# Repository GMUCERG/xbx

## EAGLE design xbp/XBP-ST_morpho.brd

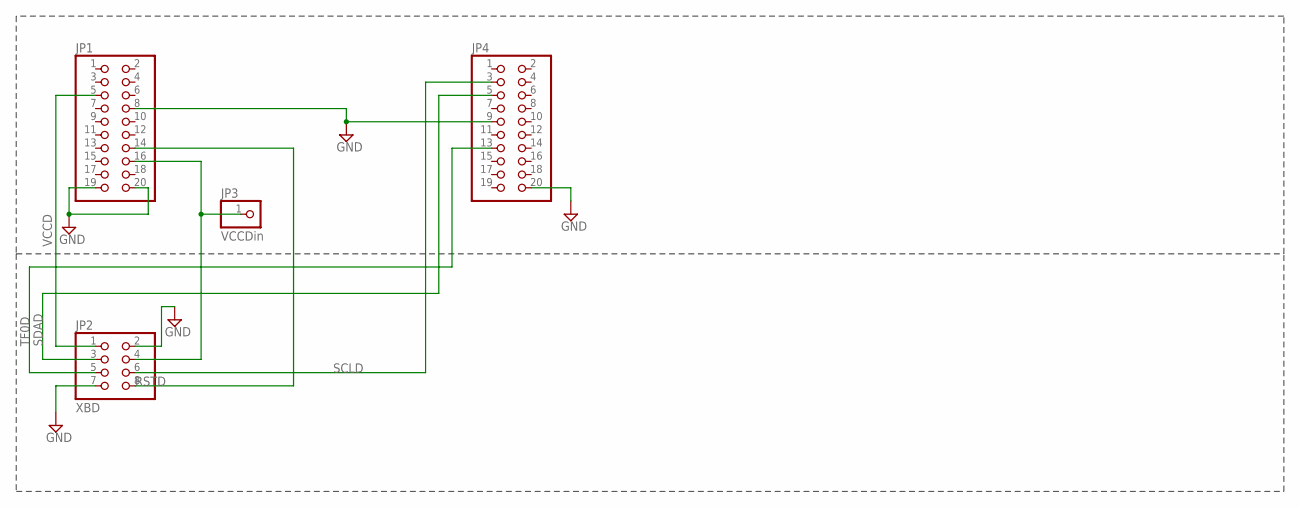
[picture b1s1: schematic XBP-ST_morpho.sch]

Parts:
JP1, JP4: PINHD-2X10; 2X10
JP2: XBD; 2X04/90
JP3: VCCDin; 1X01

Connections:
GND: JP1.8, JP1.19, JP1.20, JP2.2, JP2.7, JP4.9, JP4.20
unnamed: JP1.16, JP2.4, JP3.1
RSTD: JP1.14, JP2.8
SCLD: JP2.6, JP4.3
SDAD: JP2.3, JP4.5
TF0D: JP2.5, JP4.13
VCCD: JP1.5, JP2.1

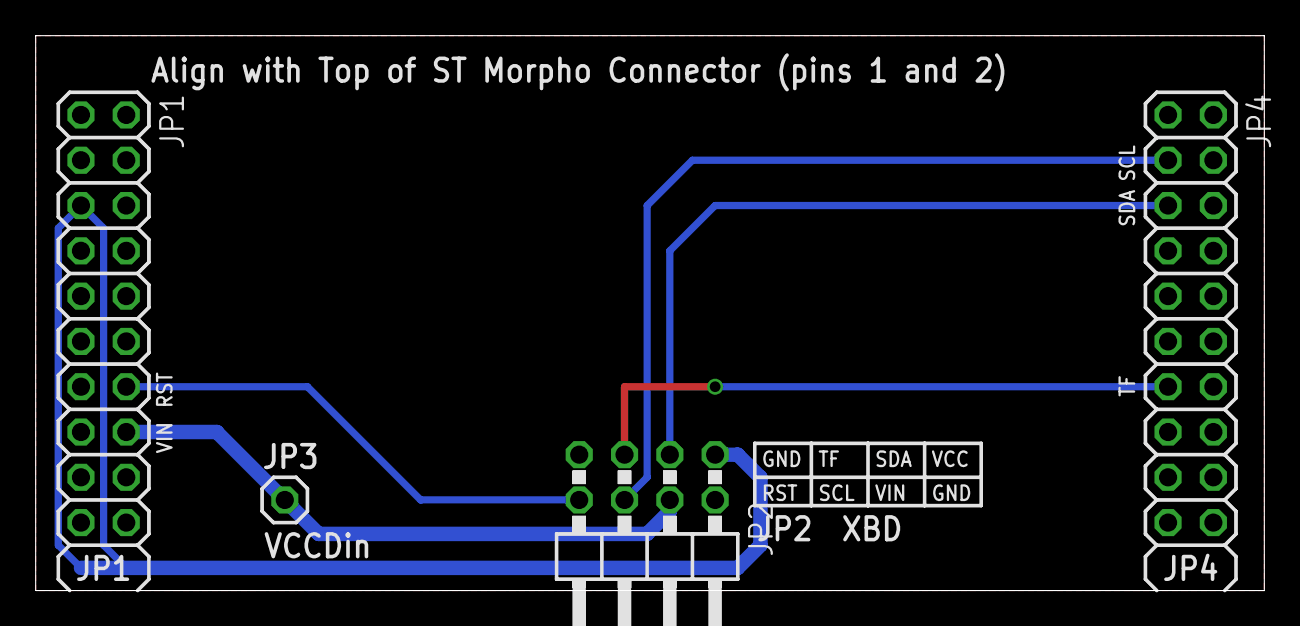
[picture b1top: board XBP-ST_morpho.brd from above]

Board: 2 copper layers, 68.9 x 31.1 mm, 4 parts (0 on the bottom side), 7 nets.

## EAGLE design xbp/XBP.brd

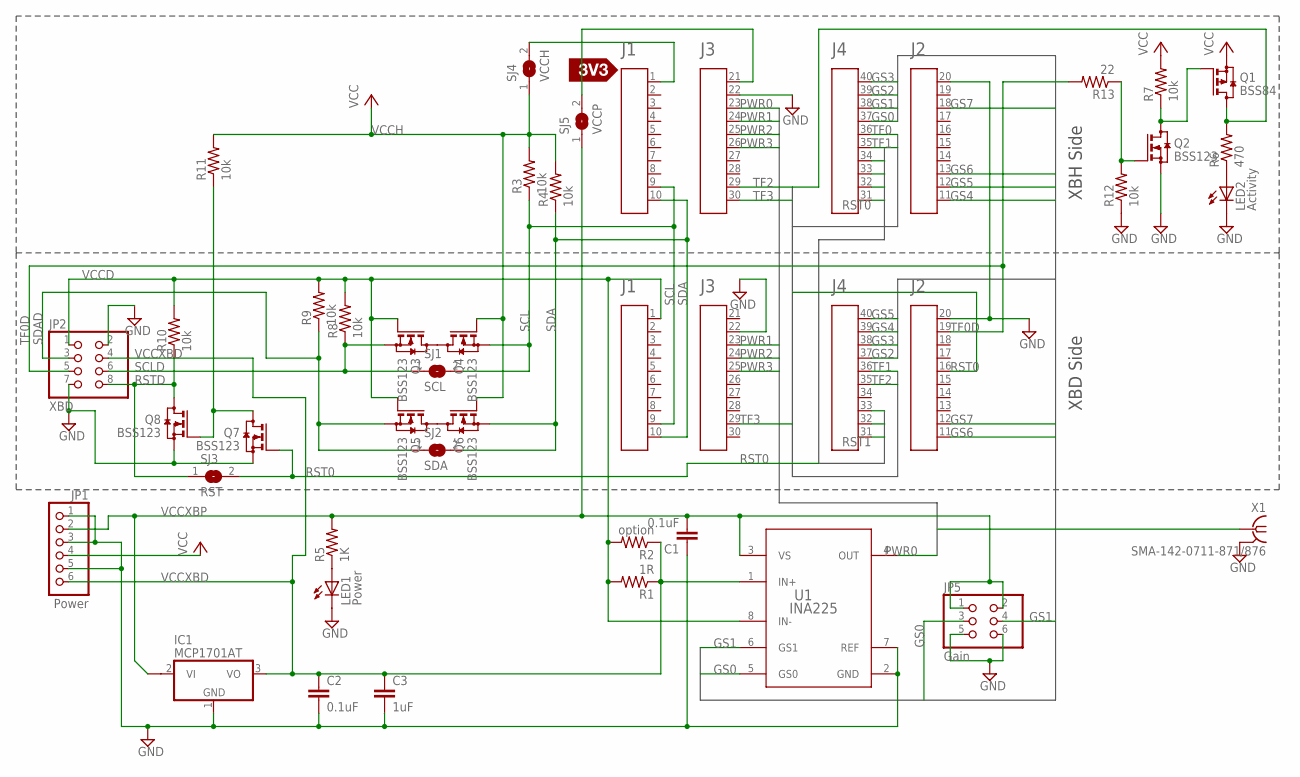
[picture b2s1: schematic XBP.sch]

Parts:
A1: XBHCon; 4X10-BOOSTERPACK
A2: XBDCon; 4X10-BOOSTERPACK
C1, C2: 0.1uF; C0603
C3: 1uF; C0603
IC1: MCP1701AT; SOT89
JP1: Power; 1X06/90
JP2: XBD; 2X04/90
JP5: Gain; 2X03
LED1: Power; CHIPLED_0603
LED2: Activity; CHIPLED_0603
Q1: BSS84; SOT23
Q2, Q3, Q4, Q5, Q6, Q7, Q8: BSS123; SOT23
R1: 1R; R1210
R2: option; R0805
R3, R4, R7, R8, R9, R10, R11, R12: 10k; R0603
R5: 1K; R0603
R6: 470; R0603
R13: 22; R0603
SJ1: SCL; SJ
SJ2: SDA; SJ
SJ3: RST; SJ
SJ4: VCCH; SJ
SJ5: VCCP; SJ
U1: INA225; DGK0008A_N
U3: SILK_3V3_TAG
X1: SMA-142-0711-871/876; J502-ND-142-0711-871/876

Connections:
GND: A1.20, A1.22, A2.20, A2.22, C1.1, C2.2, C3.2, IC1.1 (GND), JP1.1, JP1.3, JP1.5, JP2.2, JP2.7, JP5.5, JP5.6, LED1.C, LED2.C, Q2.2 (S), Q7.2 (S), Q8.2 (S), R12.1, U1.2 (GND), U1.7 (REF), X1.G@1 (2), X1.G@2 (2), X1.G@3 (2), X1.G@4 (2)
GS0: A1.37, JP5.3, U1.5 (GS0)
GS1: A1.38, JP5.4, U1.6 (GS1)
GS2: A1.39, A2.37
GS3: A1.40, A2.38
GS4: A1.11, A2.39
GS5: A1.12, A2.40
GS6: A1.13, A2.11
GS7: A1.18, A2.12
unnamed: A1.1, SJ4.2
unnamed: A1.21, SJ5.2
unnamed: LED1.A, R5.1
unnamed: Q2.1 (G), R12.2, R13.1
unnamed: LED2.A, R6.1
unnamed: Q3.3 (D), Q4.3 (D)
unnamed: Q5.3 (D), Q6.3 (D)
unnamed: Q1.1 (G), Q2.3 (D), R7.1
unnamed: Q7.3 (D), Q8.1 (G), R11.1
PWR0: A1.23, U1.4 (OUT), X1.1
PWR1: A1.24, A2.23
PWR2: A1.25, A2.24
PWR3: A1.26, A2.25
RST0: A1.31, A2.16, Q7.1 (G), SJ3.2
RST1: A1.32, A2.31
RST2: A1.33, A2.32
RST3: A1.34, A2.33
RSTD: JP2.8, Q8.3 (D), R10.1, SJ3.1
SCL: A1.9, A2.9, Q4.2 (S), R3.1, SJ1.2
SCLD: JP2.6, Q3.2 (S), R8.1, SJ1.1
SDA: A1.10, A2.10, Q6.2 (S), R4.1, SJ2.2
SDAD: JP2.3, Q5.2 (S), R9.1, SJ2.1
TF0: A1.36, Q1.3 (D), R6.2
TF0D: A2.19, JP2.5, R13.2
TF1: A1.35, A2.36
TF2: A1.29, A2.35
TF3: A1.30, A2.29
VCCD: A2.1, JP2.1, Q3.1 (G), Q5.1 (G), R1.2, R2.2, R8.2, R9.2, R10.2, U1.8 (IN-)
VCCH: JP1.4, Q1.2 (S), Q4.1 (G), Q6.1 (G), R3.2, R4.2, R7.2, R11.2, SJ4.1
VCCXBD: C2.1, C3.1, IC1.3 (VO), JP1.6, JP2.4, R1.1, R2.1, U1.1 (IN+)
VCCXBP: C1.2, IC1.2@1 (VI1), JP1.2, JP5.1, JP5.2, R5.2, SJ5.1, U1.3 (VS)

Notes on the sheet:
XBH Side
XBD Side

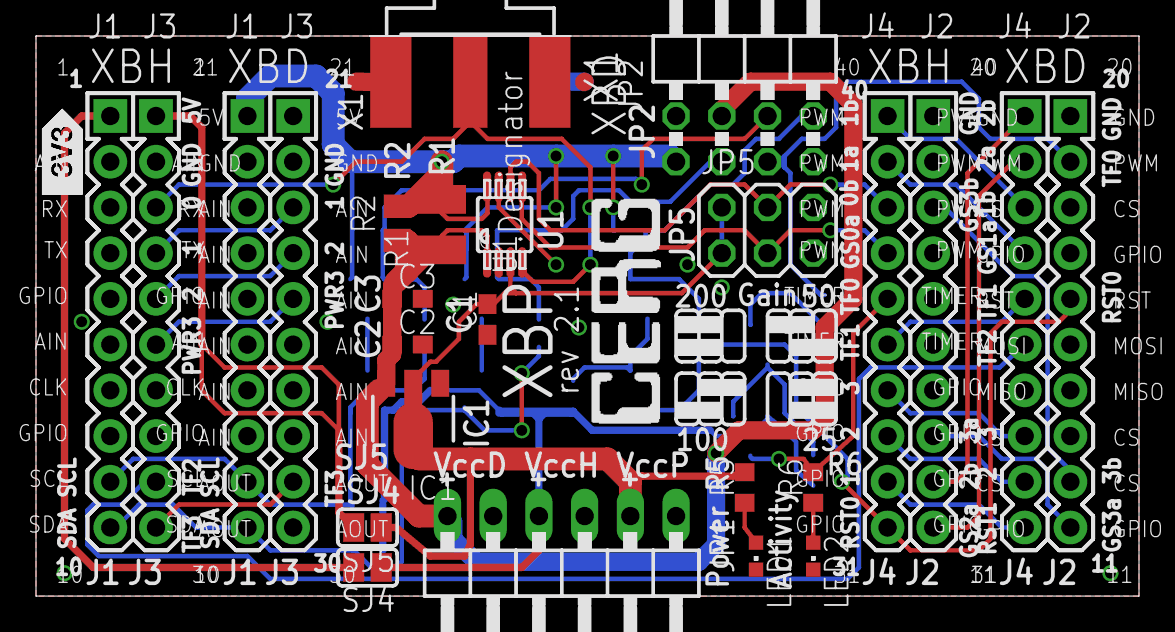
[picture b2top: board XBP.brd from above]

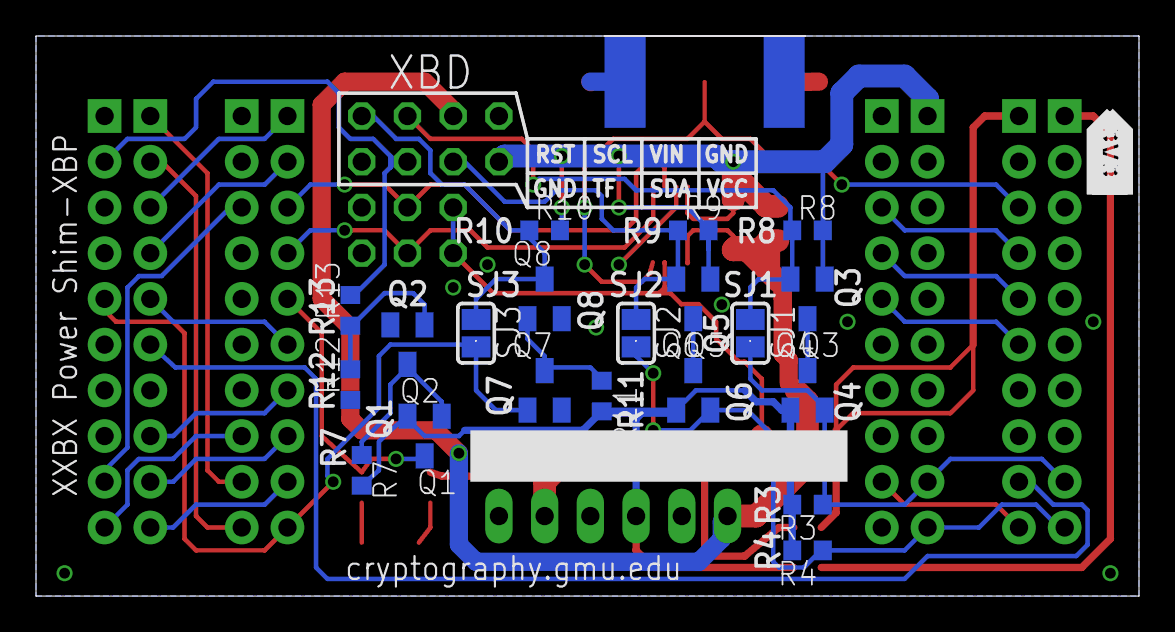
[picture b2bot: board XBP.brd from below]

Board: 2 copper layers, 61.3 x 31.1 mm, 40 parts (20 on the bottom side), 40 nets.

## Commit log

2015-09-01 Make submodules track master
2015-09-01 Update instructions, install script
2015-09-07 Fix instructions
    add instruction to setup path before running anything
    specify correct gdb
    explicitly call the .gdbinit file
2016-05-27 Update .gitmodules
    updated to new location
2016-09-30 setup.sh update
2016-10-05 some update to docs
2016-10-07 more xbds
2016-10-08 no idea
2016-10-20 added pic32
2017-02-02 fixed ip address setting instructions
2017-02-02 corrected pin assignments and added pin lables
2017-02-11 Added Notes
2017-02-12 modified xxbx notes
2017-02-17 Update XXBX Notes on timing
2017-03-09 updated xxbx_notes
2017-03-10 include SUPERCOP
2017-10-12 updates submodules xbh, xbs_xbd to their latest commits
2017-10-12 pulled updates for submodule xbs_xbd(latest changes for patform fr5994)
2017-10-24 updated algo list for TM4C129
2017-10-24 fixed mistake in algo list for TM4C129
2017-11-16 added works/error columns for each processor and compiler combination
2018-02-09 version 2.0
2018-02-12 rev2.0 submitted to OSHPark
2018-03-20 starting modifications
2018-03-21 title page draft
2018-03-22 headerlines defined
2018-03-22 new .gitignore
2018-03-23 some update
2018-03-23 editing
2018-03-23 none
2018-03-24 sensing and shifting draft done, chapters fixed in cls
2018-03-24 added lots of stuff and updated class file too
2018-03-24 gitignores
2018-03-24 git?
2018-03-24 yuck git
2018-03-24 really
2018-03-26 cleanup xbp and doc stuff
2018-03-26 more cleanup
2018-03-26 more ...
2018-03-26 added SUPERCOP submodule
2018-03-26 no idea why
2018-03-26 outline of User Guides
2018-03-26 fixed class for multiple authors
2018-03-27 updated block diagram
2018-03-28 new pictures
2018-04-02 added partslist
2018-04-04 more colors defined, MSP430 XBDs described
2018-04-04 msp430fr5994 verified
2018-04-06 updated TOC
2018-04-09 new figs
2018-04-09 imported text from Johns thesis, Girmays scholarly paper and course projects
2018-04-12 draft of STM adapter
2018-04-12 removed temporary files
2018-04-13 Added XBH-XBD protocol table
2018-04-13 corrected writing of I2C
2018-04-20 XBP version 2.1
2018-04-20 XBX ST morpho Adapter version 1.0
2018-04-20 new poster
2018-04-25 Poster draft
2018-04-26 added more text
2018-04-29 XXBX flow chart
2018-04-30 first colum ready for review
2018-04-30 updated flow with parameter loop
2018-04-30 updated poster with ROM and RAM usage
2018-04-30 Poster ready for review, missing results
2018-05-01 poster done
2018-11-07 SCL was not connected to ST Morpho Pin
2018-11-21 added XBH installation instructions
2018-11-21 new figure
2018-11-29 added notes for xbd bootloader compilation
2018-11-29 added notes for sw installation
2019-05-23 added styles for paper
2019-05-23 Converted paper to latex w/o graphs or tables
2019-05-28 added some diagrams and references
2019-05-28 done with 1st round of edits
2019-06-03 submitted to NIST
2019-06-15 Added KEM/Sign support
2019-07-15 XXBX install and compilation of XBH and XBD on clean Kubuntu 18.04 documented
2019-07-19 ran all kems that are round 2 and in config.ini
2019-07-19 finally sike751 is done
2019-07-19 more files to install
2019-07-22 almost ready for final submission
2019-07-27 XBD-UserGuide added description tm4c123
2019-08-21 results for 2nd PQC conference
2019-08-21 fig in png
2019-10-18 xxbx block figure updated
